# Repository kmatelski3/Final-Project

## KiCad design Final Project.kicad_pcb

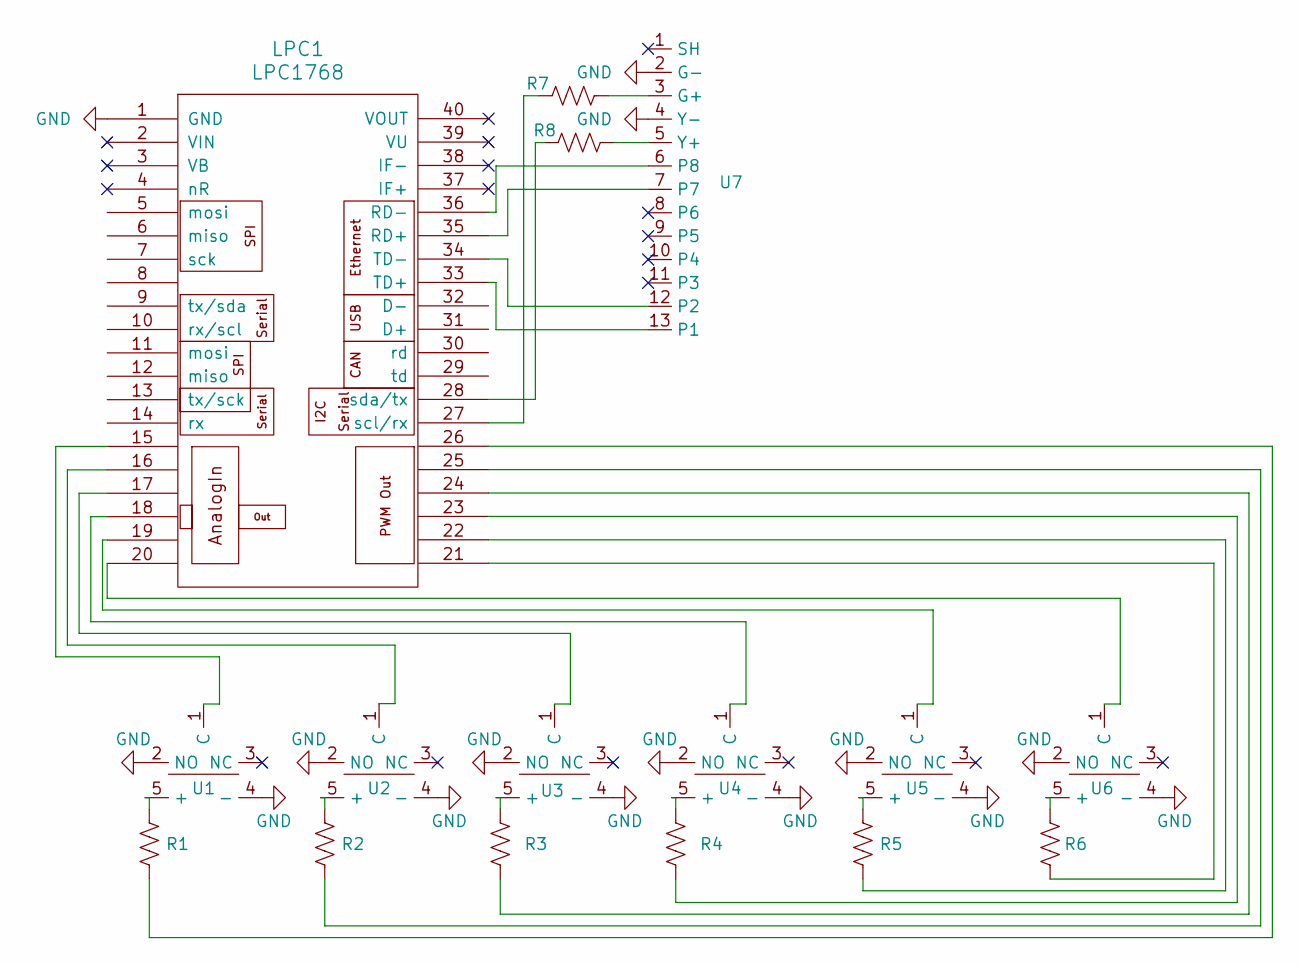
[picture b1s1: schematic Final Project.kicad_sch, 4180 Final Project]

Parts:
LPC1: LPC1768
R1, R2, R3, R4, R5, R6: 300; R_0805_2012Metric_Pad1.20x1.40mm_HandSolder
R7, R8: R_US; R_0805_2012Metric_Pad1.20x1.40mm_HandSolder
U1, U2, U3, U4, U5, U6: LED Switch
U7: PinHeader_1x13_P2.54mm_Vertical

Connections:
GND: LPC1.1 (GND), U1.2 (NO), U1.4 (-), U2.2 (NO), U2.4 (-), U3.2 (NO), U3.4 (-), U4.2 (NO), U4.4 (-), U5.2 (NO), U5.4 (-), U6.2 (NO), U6.4 (-), U7.2 (G-), U7.4 (Y-)
unnamed: LPC1.21, R6.1
unnamed: LPC1.22, R5.1
unnamed: LPC1.23, R4.1
unnamed: LPC1.24, R3.2
unnamed: LPC1.25, R2.1
unnamed: LPC1.26, R1.1
unnamed: LPC1.35 (RD+), U7.7
unnamed: LPC1.36 (RD-), U7.6 (P8)
unnamed: LPC1.33 (TD+), U7.13 (P1)
unnamed: LPC1.34 (TD-), U7.12 (P2)
unnamed: LPC1.27 (scl/rx), R7.1
unnamed: LPC1.28 (sda/tx), R8.1
unnamed: R1.2, U1.5 (+)
unnamed: LPC1.15, U1.1 (C)
unnamed: R2.2, U2.5 (+)
unnamed: LPC1.16, U2.1 (C)
unnamed: R3.1, U3.5 (+)
unnamed: LPC1.17, U3.1 (C)
unnamed: R4.2, U4.5 (+)
unnamed: LPC1.18, U4.1 (C)
unnamed: R5.2, U5.5 (+)
unnamed: LPC1.19, U5.1 (C)
unnamed: R6.2, U6.5 (+)
unnamed: LPC1.20, U6.1 (C)
unnamed: R7.2, U7.3 (G+)
unnamed: R8.2, U7.5 (Y+)

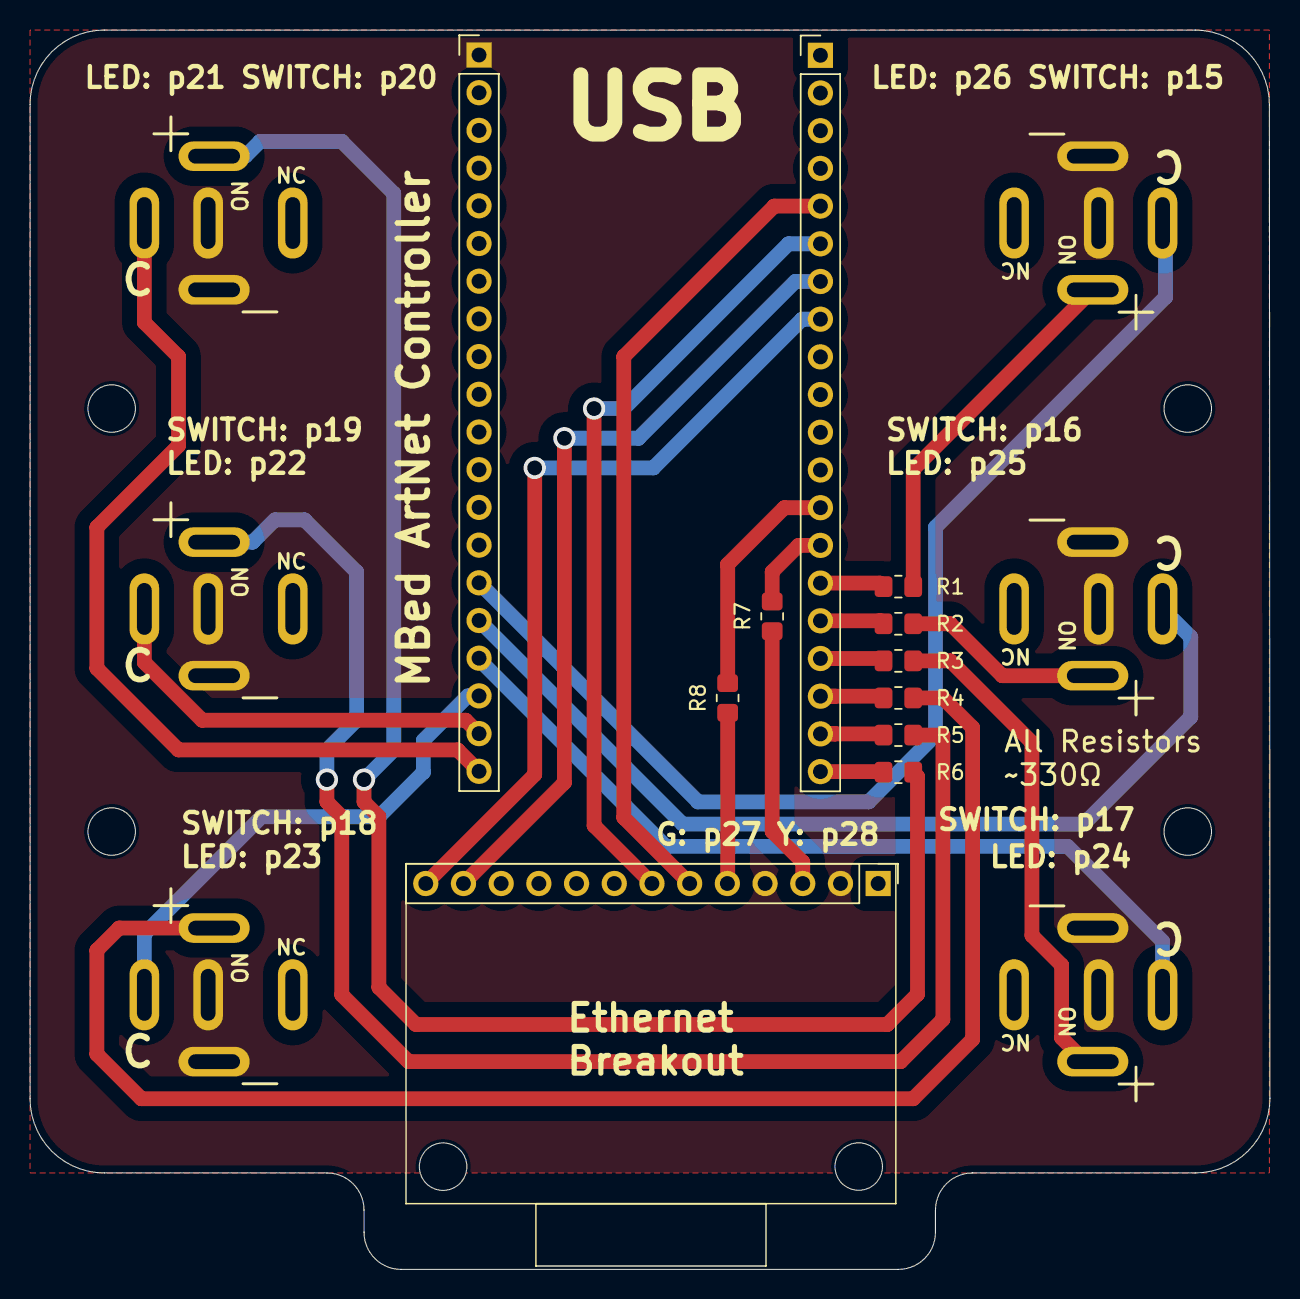
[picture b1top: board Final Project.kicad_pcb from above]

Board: 2 copper layers, 83.5 x 83.5 mm, 16 parts (0 on the bottom side), 27 nets.

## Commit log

2024-04-25 All the files
2024-04-25 3D Print Files
